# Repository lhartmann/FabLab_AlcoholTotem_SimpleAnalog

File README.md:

# Gel Dispenser Controller

This is a simple analog control circuit intended to trigger and dose hand sanitizer dispensers.

Features:
- Touch-less triggering: Hand detector based on IR reflectivity.
- Sensitivity and dose configurable via trimpots.
- Fully analog circuit.
- Single-rail 5V operation: USB and battery-bank friendly.
- Compact, single-sided PCB: Only 38x28mm.

Designed for FabLab UFPB, as part of a KiCad training session.

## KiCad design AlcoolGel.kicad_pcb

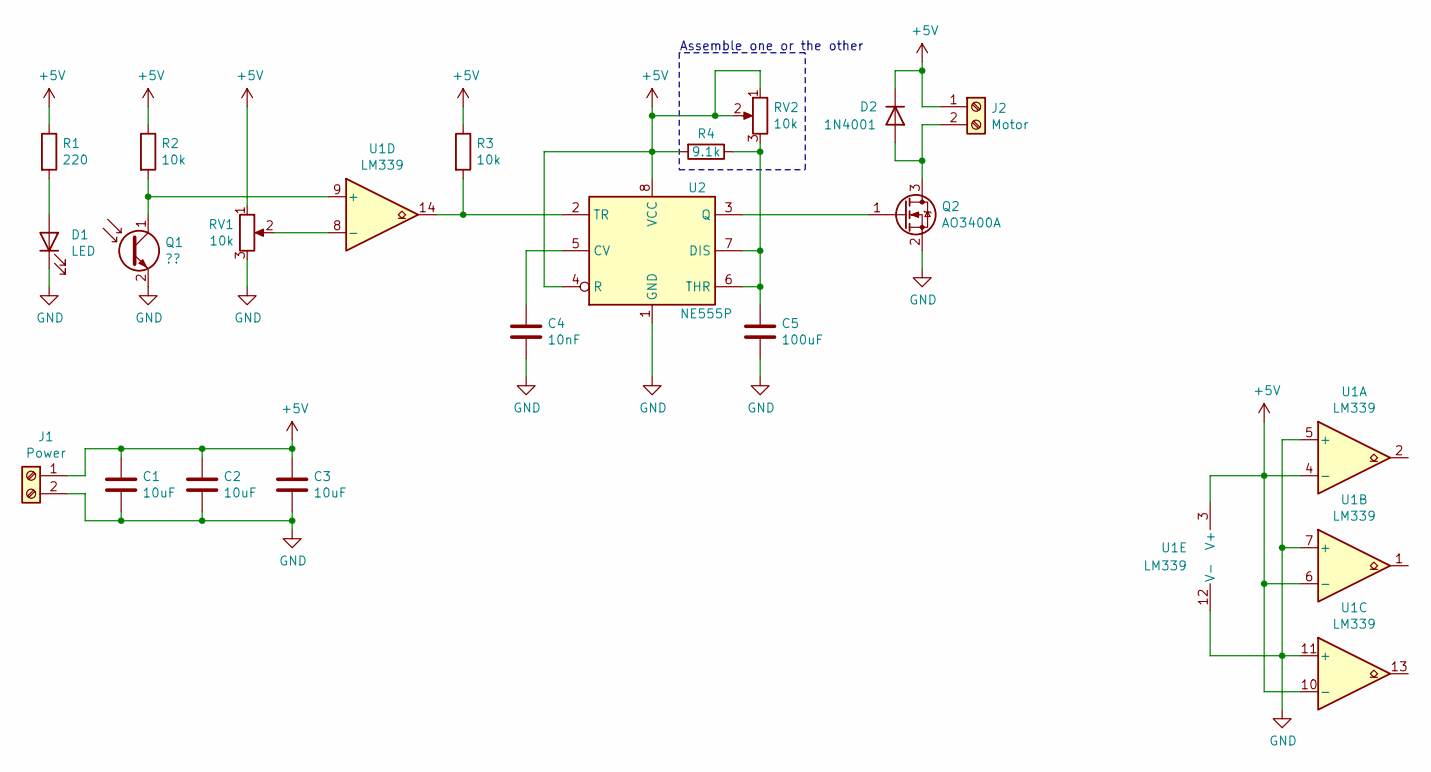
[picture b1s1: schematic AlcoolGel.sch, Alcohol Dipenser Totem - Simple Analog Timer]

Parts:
C1, C2, C3: 10uF; C_0805_2012Metric_Pad1.18x1.45mm_HandSolder
C4: 10nF; C_0805_2012Metric_Pad1.18x1.45mm_HandSolder
C5: 100uF; C_0805_2012Metric_Pad1.18x1.45mm_HandSolder
D1: LED; PinHeader_1x02_P2.54mm_Vertical
D2: 1N4001; D_DO-41_SOD81_P10.16mm_Horizontal
J1: Power; TerminalBlock_Phoenix_MKDS-3-2-5.08_1x02_P5.08mm_Horizontal
J2: Motor; TerminalBlock_Phoenix_MKDS-3-2-5.08_1x02_P5.08mm_Horizontal
Q1: ??; PinHeader_1x02_P2.54mm_Vertical
Q2: AO3400A; SOT-23
R1: 220; R_0805_2012Metric_Pad1.20x1.40mm_HandSolder
R2, R3: 10k; R_0805_2012Metric_Pad1.20x1.40mm_HandSolder
R4: 9.1k; R_0805_2012Metric_Pad1.20x1.40mm_HandSolder
RV1, RV2: 10k; Potentiometer_Bourns_3296W_Vertical
U1: LM339; DIP-14_W7.62mm_LongPads
U2: NE555P; DIP-8_W7.62mm_LongPads

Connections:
+5V: C1.1, C2.1, C3.1, D2.1 (K), J1.1, J2.1, R1.1, R2.1, R3.1, R4.2, RV1.1, RV2.1, RV2.2, U1.3 (V+), U1.4 (-), U1.6 (-), U1.10 (-), U2.4 (R), U2.8 (VCC)
GND: C1.2, C2.2, C3.2, C4.2, C5.2, D1.1 (K), J1.2, Q1.2 (E), Q2.2 (S), RV1.3, U1.5 (+), U1.7 (+), U1.11 (+), U1.12 (V-), U2.1 (GND)
unnamed: C4.1, U2.5 (CV)
unnamed: C5.1, R4.1, RV2.3, U2.6 (THR), U2.7 (DIS)
unnamed: D1.2 (A), R1.2
unnamed: D2.2 (A), J2.2, Q2.3 (D)
unnamed: Q1.1 (C), R2.2, U1.9 (+)
unnamed: Q2.1 (G), U2.3 (Q)
unnamed: R3.2, U1.14, U2.2 (TR)
unnamed: RV1.2, U1.8 (-)

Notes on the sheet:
Assemble one or the other

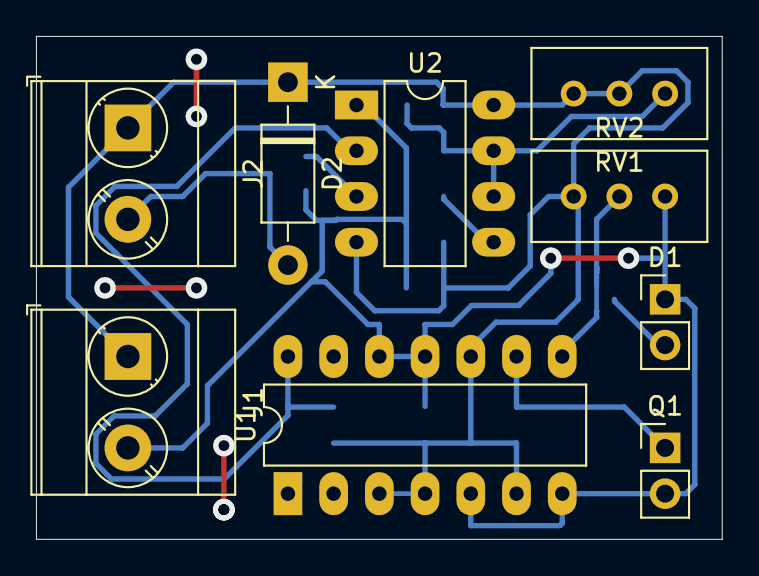
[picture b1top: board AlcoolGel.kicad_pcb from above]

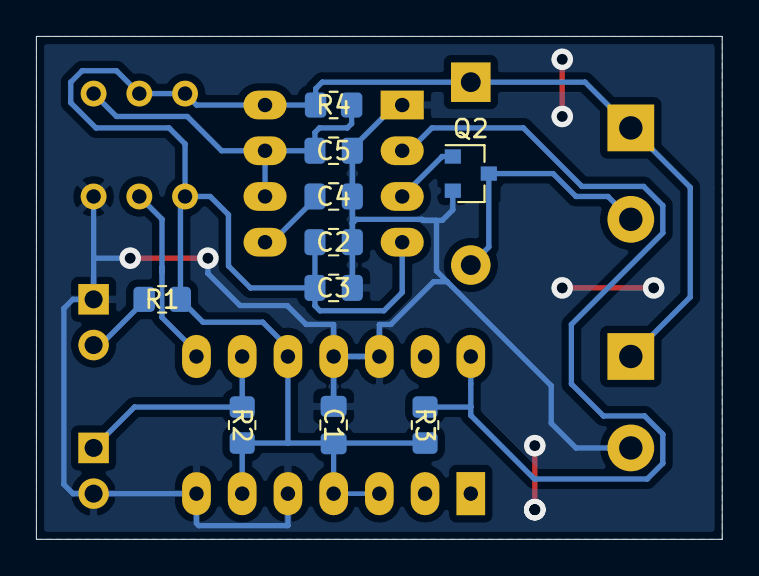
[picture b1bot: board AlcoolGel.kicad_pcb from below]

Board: 2 copper layers, 38.1 x 27.9 mm, 19 parts (10 on the bottom side), 10 nets.

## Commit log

2020-10-22 Updated gitignore.
2020-10-22 Initial commit.
2020-10-22 Update README.
2020-10-22 Moved pictures to github issues.

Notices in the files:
AlcoolGel.sch:
(c) 2020 Lucas V. Hartmann
